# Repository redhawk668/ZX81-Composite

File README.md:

# ZX81 Composite Video with Backporch
This PCB provides composite video for the ZX81, it replaces the internal PCB from the modulator. For ZX81's with earlier type ULA's it generates a back porch signal.

It will work with the later 2C210 ULA. However, this ULA does provide a backporch signal, so the 555 timer chip is not needed and can be removed. It is based on instructions and schematics found on zx.zigg.net.

# Billing of Materials:

|Qty |Value  |Component                   |Package       |PCB      |
|----|-------|----------------------------|--------------|---------|
| 2x | 10K   | Metal Film Resistors       | Axial DIN204 | R1, R2  |  
| 1x | 68R   | Metal Film Resistor        | Axial DIN204 | R3      |
| 1x | 56R   | Metal Film Resistor        | Axial DIN204 | R4      |
| 1x | 10nF  | Ceramic Capacitor          | Disc 5mm     | C2      |
| 1x | 820pF | Ceramic Capacitor          | Disc 5mm     | C3      |
| 1x | 82pF  | Ceramic Capacitor          | Disc 5mm     | C4      |
| 1x | 22uF  | Electrolytic Capacitor     | Radial 6.3mm | C1      |
| 2x | 1N4148| Diodes                     | DO-35        | D1, D2  |
| 2x | BC337 | Transistors                | TO-92        | Q1, Q2  |
| U1 | NE555 | Timer IC                   | DIP-8        | U1      |
--------------------------------------------------------------------

# Usage:
Desolder the modulator case, remove the PCB and solder the new PCB in. Solder wires to the +5 volt input, video input and video output. Re-assemble the modulator case and solder it back on the ZX81 board. Connect video output with the RCA, connect +5 volt and video in with the correspending pads on the ZX81 board.

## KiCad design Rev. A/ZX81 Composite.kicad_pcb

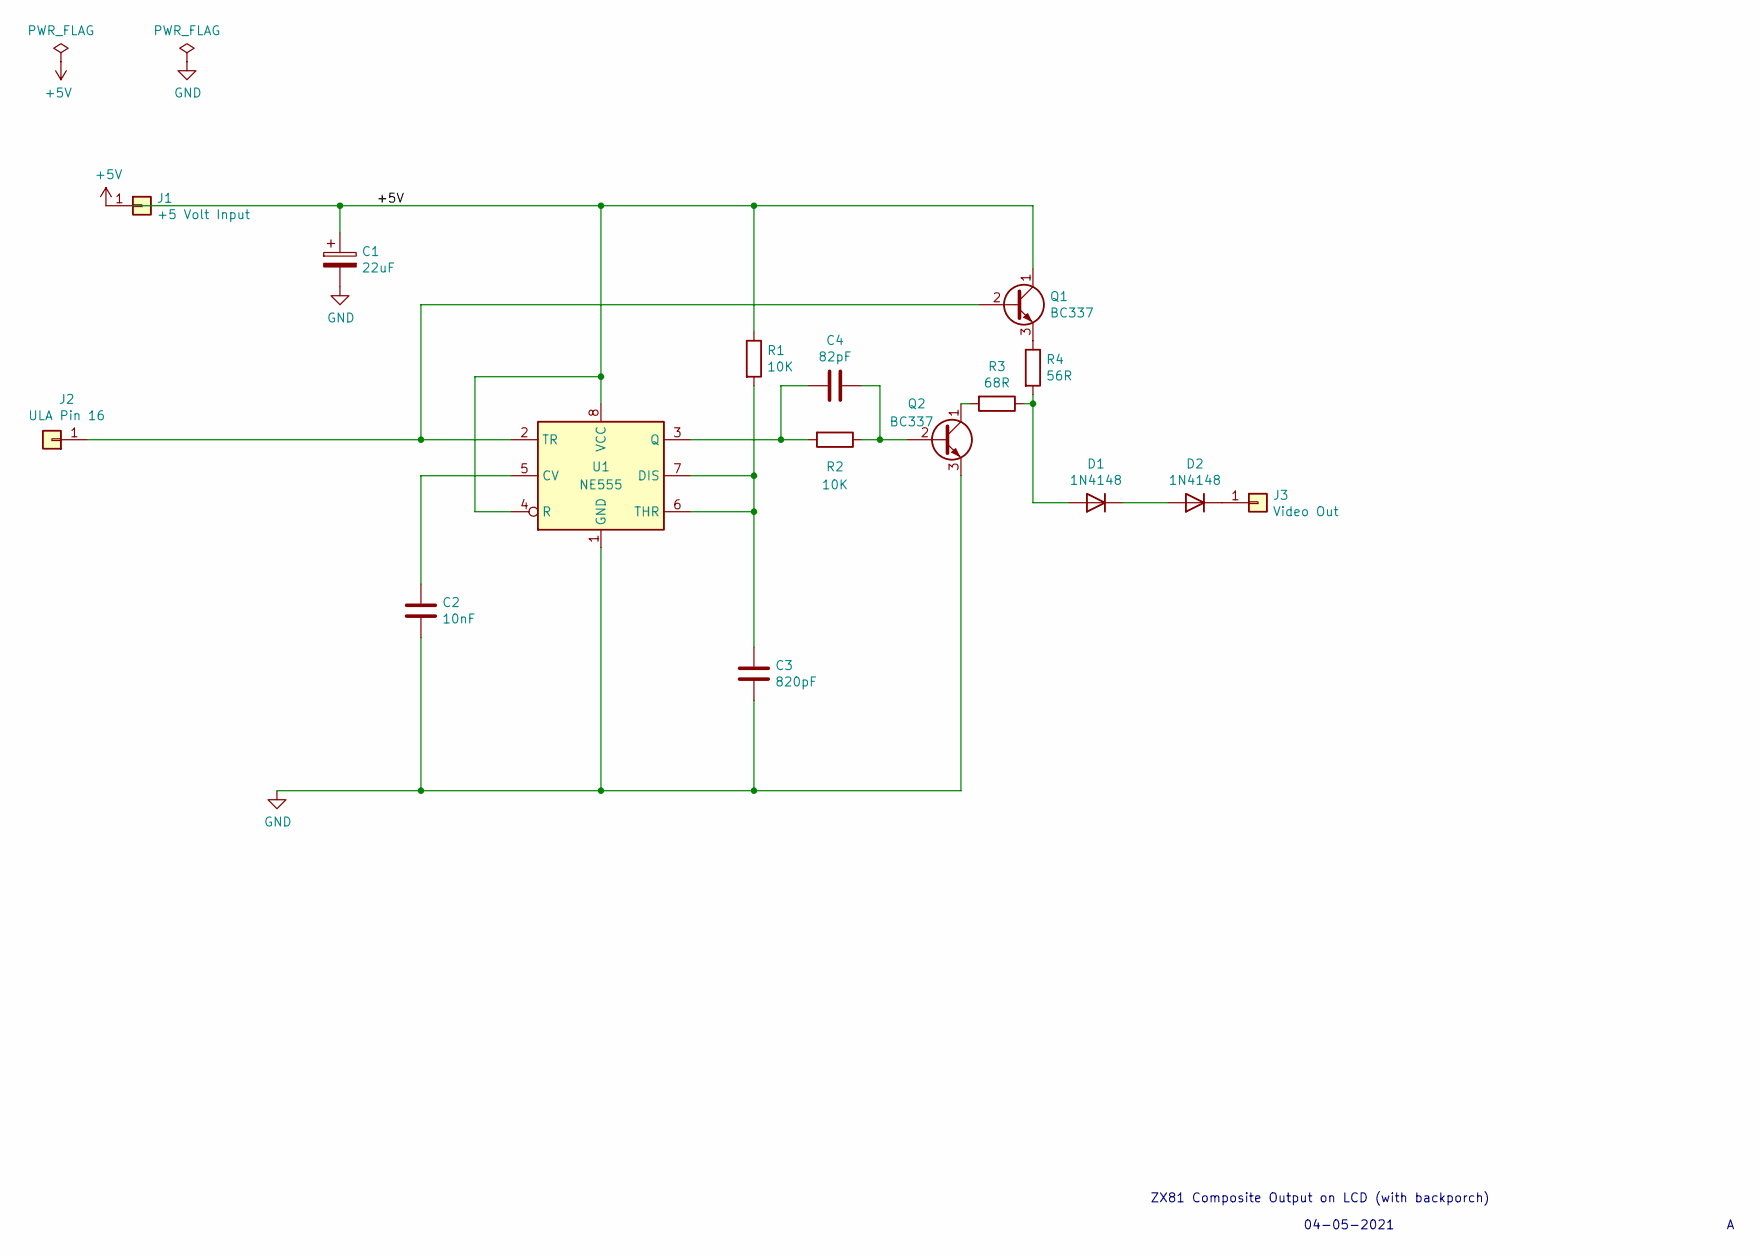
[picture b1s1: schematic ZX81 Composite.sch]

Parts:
C1: 22uF; CP_Radial_D6.3mm_P2.50mm
C2: 10nF; C_Disc_D5.0mm_W2.5mm_P5.00mm
C3: 820pF; C_Disc_D5.0mm_W2.5mm_P5.00mm
C4: 82pF; C_Disc_D5.0mm_W2.5mm_P5.00mm
D1, D2: 1N4148; D_DO-35_SOD27_P7.62mm_Horizontal
J1: +5 Volt Input; Pin_Header_Straight_1x01_Pitch2.54mm
J2: ULA Pin 16; Pin_Header_Straight_1x01_Pitch2.54mm
J3: Video Out; Pin_Header_Straight_1x01_Pitch2.54mm
Q1, Q2: BC337; TO-92_Inline_Narrow_Oval
R1, R2: 10K; R_Axial_DIN0204_L3.6mm_D1.6mm_P5.08mm_Horizontal
R3: 68R; R_Axial_DIN0204_L3.6mm_D1.6mm_P5.08mm_Horizontal
R4: 56R; R_Axial_DIN0204_L3.6mm_D1.6mm_P5.08mm_Horizontal
U1: NE555; DIP-8_W7.62mm

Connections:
+5V: C1.1, J1.1, Q1.1 (C), R1.1, U1.4 (R), U1.8 (VCC)
GND: C1.2, C2.2, C3.2, Q2.3 (E), U1.1 (GND)
unnamed: C2.1, U1.5 (CV)
unnamed: C3.1, R1.2, U1.6 (THR), U1.7 (DIS)
unnamed: C4.1, Q2.2 (B), R2.1
unnamed: C4.2, R2.2, U1.3 (Q)
unnamed: D1.1 (K), D2.2 (A)
unnamed: D1.2 (A), R3.1, R4.2
unnamed: D2.1 (K), J3.1
unnamed: J2.1, Q1.2 (B), U1.2 (TR)
unnamed: Q1.3 (E), R4.1
unnamed: Q2.1 (C), R3.2

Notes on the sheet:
ZX81 Composite Output on LCD (with backporch)
04-05-2021

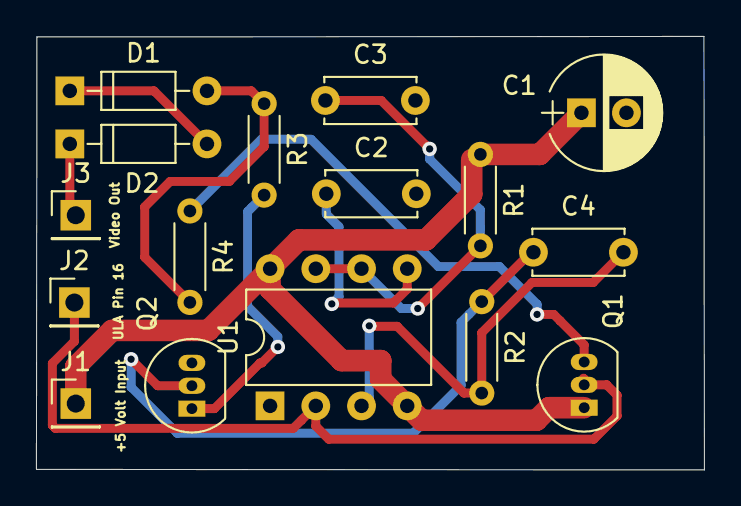
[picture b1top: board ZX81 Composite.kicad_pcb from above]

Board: 2 copper layers, 37.1 x 24.1 mm, 16 parts (0 on the bottom side), 12 nets.
